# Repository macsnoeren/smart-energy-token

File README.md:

# smart-energy-token
Development of a token infrastructure for TU/e Team RED (www.teamred.nl)

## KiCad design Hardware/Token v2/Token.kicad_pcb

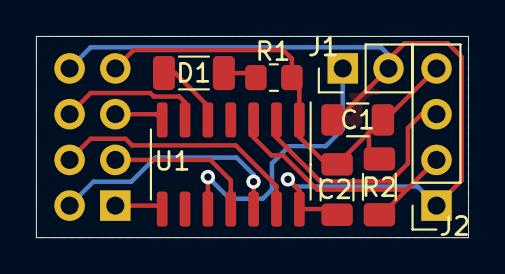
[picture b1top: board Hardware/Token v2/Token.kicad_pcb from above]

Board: 2 copper layers, 24.0 x 11.2 mm, 9 parts (1 on the bottom side), 13 nets.

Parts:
C1: 10nF; C_1206_3216Metric
C2: 10uF; C_1206_3216Metric
D1: LED; L_1206_3216Metric_Pad1.22x1.90mm_HandSolder
J1: Conn_01x02_Male; PinHeader_1x02_P2.54mm_Vertical
J2: Conn_01x04_Female; PinSocket_1x04_P2.54mm_Vertical
J4: Conn_02x04_Odd_Even; PinSocket_2x04_P2.54mm_Vertical
R1: 220; R_0805_2012Metric_Pad1.20x1.40mm_HandSolder
R2: 500k; R_1206_3216Metric_Pad1.30x1.75mm_HandSolder
U1: ATtiny1604-SS; SOIC-14_3.9x8.7mm_P1.27mm

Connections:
CE: J4.6, U1.6
CSN: J4.5, U1.7
DATA_BOTTOM: J4.3, U1.11
DATA_BOTTOM_CLK: J4.4, U1.13
DATA_TOP: J2.2, R2.1, U1.3
DATA_TOP_CLK: J2.3, U1.2
GND: C1.2, C2.2, J1.2, J2.1, J4.8, U1.14
IRQ: J4.1, U1.8
MISO: J4.2, U1.12
unnamed: D1.1, U1.5
unnamed: D1.2, R1.1
UPDI: J1.1, U1.10
VCC: C1.1, C2.1, J2.4, J4.7, R1.2, R2.2, U1.1

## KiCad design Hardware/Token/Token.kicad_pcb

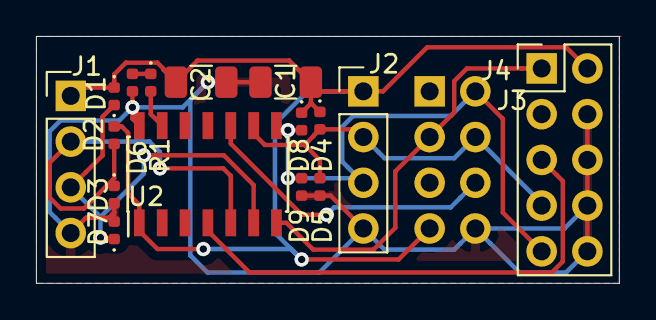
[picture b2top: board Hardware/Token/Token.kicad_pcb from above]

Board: 2 copper layers, 32.4 x 13.7 mm, 17 parts (1 on the bottom side), 11 nets.

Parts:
C1: 10nF; C_1206_3216Metric
C2: 10uF; C_1206_3216Metric
D1: LED; LED_0402_1005Metric
D2, D3, D4, D5, D6, D7, D8, D9: D_Small; D_0402_1005Metric
J1, J2: Conn_01x04_Male; PinHeader_1x04_P2.54mm_Vertical
J3: Conn_02x05_Odd_Even; PinHeader_2x05_P2.54mm_Vertical
J4: Conn_02x04_Odd_Even; PinSocket_2x04_P2.54mm_Vertical
R1: R_Small; D_0402_1005Metric
U2: ATtiny841-SSU; SOIC-14_3.9x8.7mm_P1.27mm

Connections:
CE: J4.6, U2.10
GND: C1.2, C2.2, D1.1, D3.2, D5.2, D7.2, D9.2, J1.4, J2.4, J3.4, J3.6, J3.8, J3.10, J4.8, U2.14
MOSI: J3.1, J4.3, U2.7
unnamed: D1.2, R1.1
unnamed: R1.2, U2.13
RESET: J3.5, U2.4
RXD1_SCK: D4.2, D5.1, J2.2, J3.7, J4.4, U2.9
RX_BUILDING: D6.2, D7.1, J1.3, U2.6
TXD1_MISO: D8.2, D9.1, J2.3, J3.9, J4.2, U2.8
TX_BUILDING: D2.2, D3.1, J1.2, U2.5
VCC: C1.1, C2.1, D2.1, D4.1, D6.1, D8.1, J1.1, J2.1, J3.2, J4.7, U2.1

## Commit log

2021-03-22 Last project files
2021-03-22 Added models 3D printing
2021-03-23 Added a new version, which is much smaller simpler
2021-03-23 Updated some files for documentation
2021-04-08 Init commit for the token code
2021-04-09 Implemented reveiving
2021-04-10 Created a new version of the hardware token v2
2021-04-12 Init statemachine build
2021-04-13 First working statemachine verion
2021-04-13 Improved send flow
2021-04-14 Stable version
2021-04-15 Improved speed and reliabilty of the tokens
2021-04-16 Improved speed and reliablity
2021-04-16 Improved more but still sometimes chrash. But seems to be hardware issue
2021-04-16 Made the variables for sending in 1 place
2021-04-19 Improved the token code and started the python receiver script
2021-04-20 Removed env folder from github and improved some stuff
2021-04-21 Extra tokens is working yesss.
2021-05-18 added code for new token
2021-05-19 Changed the python receiver code to new version and improved the code for the tokens
2021-05-21 3th token now works arduino delay blocked the code
2021-05-21 Speeded up the protocol and added reset when stuck on wrong state
2021-05-21 improved the speed even more
2021-05-27 Improved Interrupt
2021-06-07 Added new gateway code and improved the token code
2021-06-08 Improved the code a bit
2021-06-09 Clean up a bit of the code
2021-06-09 Improved gateway and new verison of serialnumbers
2021-07-01 Improved software
2021-07-05 Added more codes
2021-07-05 added build code and improved gitignore
